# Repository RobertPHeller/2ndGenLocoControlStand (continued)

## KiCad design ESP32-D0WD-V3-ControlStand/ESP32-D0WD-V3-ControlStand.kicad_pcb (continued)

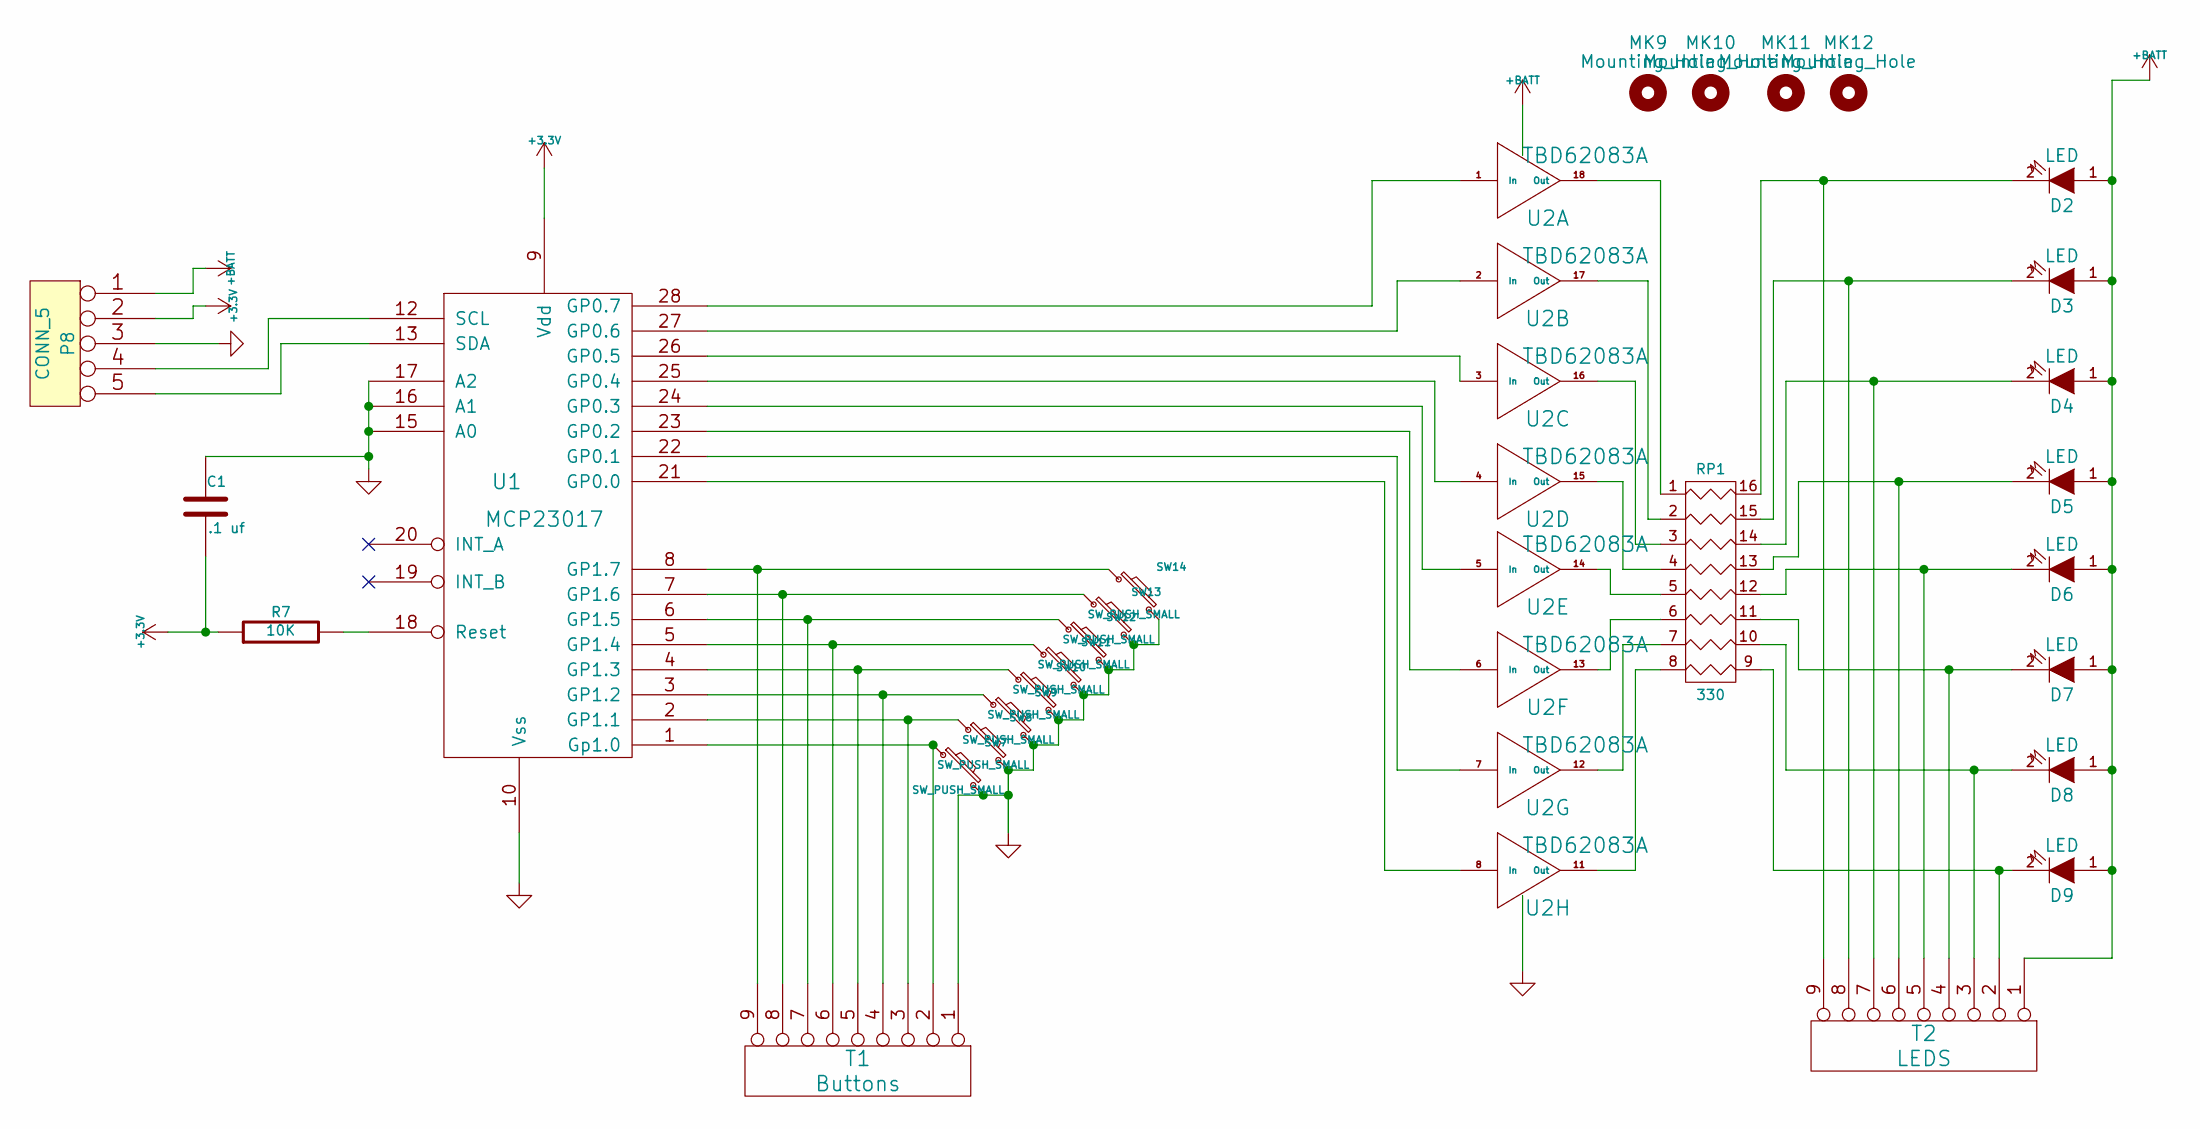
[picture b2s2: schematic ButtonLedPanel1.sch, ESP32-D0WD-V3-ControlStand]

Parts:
C1: .1 uf; C_0603; Mouser Part Number 710-885012206095
D2, D3, D4, D5, D6, D7, D8, D9: LED; LED_D5.0mm
MK9, MK10, MK11, MK12: Mounting_Hole; MountingHole_2.5mm
P8: CONN_5; Pin_Header_Angled_1x05_Pitch2.54mm; Mouser Part Number 649-1012937990501BLF
R7: 10K; R_0402; Mouser Part Number 603-RC0402JR-0710KL
RP1: 330; 4816P; Mouser Part Number 652-4816P-T1LF-330
SW7, SW8, SW9, SW10, SW11, SW12, SW13, SW14: SW_PUSH_SMALL; SW_PUSH_6mm; Mouser Part Number 179-TS026660BK160LCR
T1: Buttons; TerminalBlock_Pheonix_MPT-2.54mm_9pol; Mouser Part Number 651-1725724
T2: LEDS; TerminalBlock_Pheonix_MPT-2.54mm_9pol; Mouser Part Number 651-1725724
U1: MCP23017; SOIC-28W_7.5x17.9mm_Pitch1.27mm; Mouser Part Number 579-MCP23017-E/SO
U2: TBD62083A; SOIC-18W_7.5x11.6mm_Pitch1.27mm; Mouser Part Number 757-TBD62083AFG

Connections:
+3V3: C1.2, P8.2, R7.1, U1.9 (Vdd); also elsewhere on the board
+BATT: D2.1 (A), D3.1 (A), D4.1 (A), D5.1 (A), D6.1 (A), D7.1 (A), D8.1 (A), D9.1 (A), P8.1, T2.1, U2.10 (OC); also elsewhere on the board
GND: C1.1, P8.3, SW7.2, SW8.2, SW9.2, SW10.2, SW11.2, SW12.2, SW13.2, SW14.2, T1.1, U1.10 (Vss), U1.15 (A0), U1.16 (A1), U1.17 (A2), U2.9 (IC); also elsewhere on the board
unnamed: D2.2 (K), RP1.16 (R1), T2.9
unnamed: D3.2 (K), RP1.15 (R2), T2.8
unnamed: D4.2 (K), RP1.14 (R3), T2.7
unnamed: D5.2 (K), RP1.13 (R4), T2.6
unnamed: D6.2 (K), RP1.12 (R5), T2.5
unnamed: D7.2 (K), RP1.11 (R6), T2.4
unnamed: D8.2 (K), RP1.10 (R7), T2.3
unnamed: D9.2 (K), RP1.9 (R8), T2.2
unnamed: P8.4, U1.12 (SCL)
unnamed: P8.5, U1.13 (SDA)
unnamed: R7.2, U1.18 (Reset)
unnamed: RP1.1, U2.18 (Out)
unnamed: RP1.2, U2.17 (Out)
unnamed: RP1.3, U2.16 (Out)
unnamed: RP1.4, U2.15 (Out)
unnamed: RP1.5, U2.14 (Out)
unnamed: RP1.6, U2.13 (Out)
unnamed: RP1.7, U2.12 (Out)
unnamed: RP1.8, U2.11 (Out)
unnamed: SW7.1, T1.2, U1.1 (Gp1.0)
unnamed: SW8.1, T1.3, U1.2 (GP1.1)
unnamed: SW9.1, T1.4, U1.3 (GP1.2)
unnamed: SW10.1, T1.5, U1.4 (GP1.3)
unnamed: SW11.1, T1.6, U1.5 (GP1.4)
unnamed: SW12.1, T1.7, U1.6 (GP1.5)
unnamed: SW13.1, T1.8, U1.7 (GP1.6)
unnamed: SW14.1, T1.9, U1.8 (GP1.7)
unnamed: U1.21 (GP0.0), U2.8 (In)
unnamed: U1.22 (GP0.1), U2.7 (In)
unnamed: U1.23 (GP0.2), U2.6 (In)
unnamed: U1.24 (GP0.3), U2.5 (In)
unnamed: U1.25 (GP0.4), U2.4 (In)
unnamed: U1.26 (GP0.5), U2.3 (In)
unnamed: U1.27 (GP0.6), U2.2 (In)
unnamed: U1.28 (GP0.7), U2.1 (In)

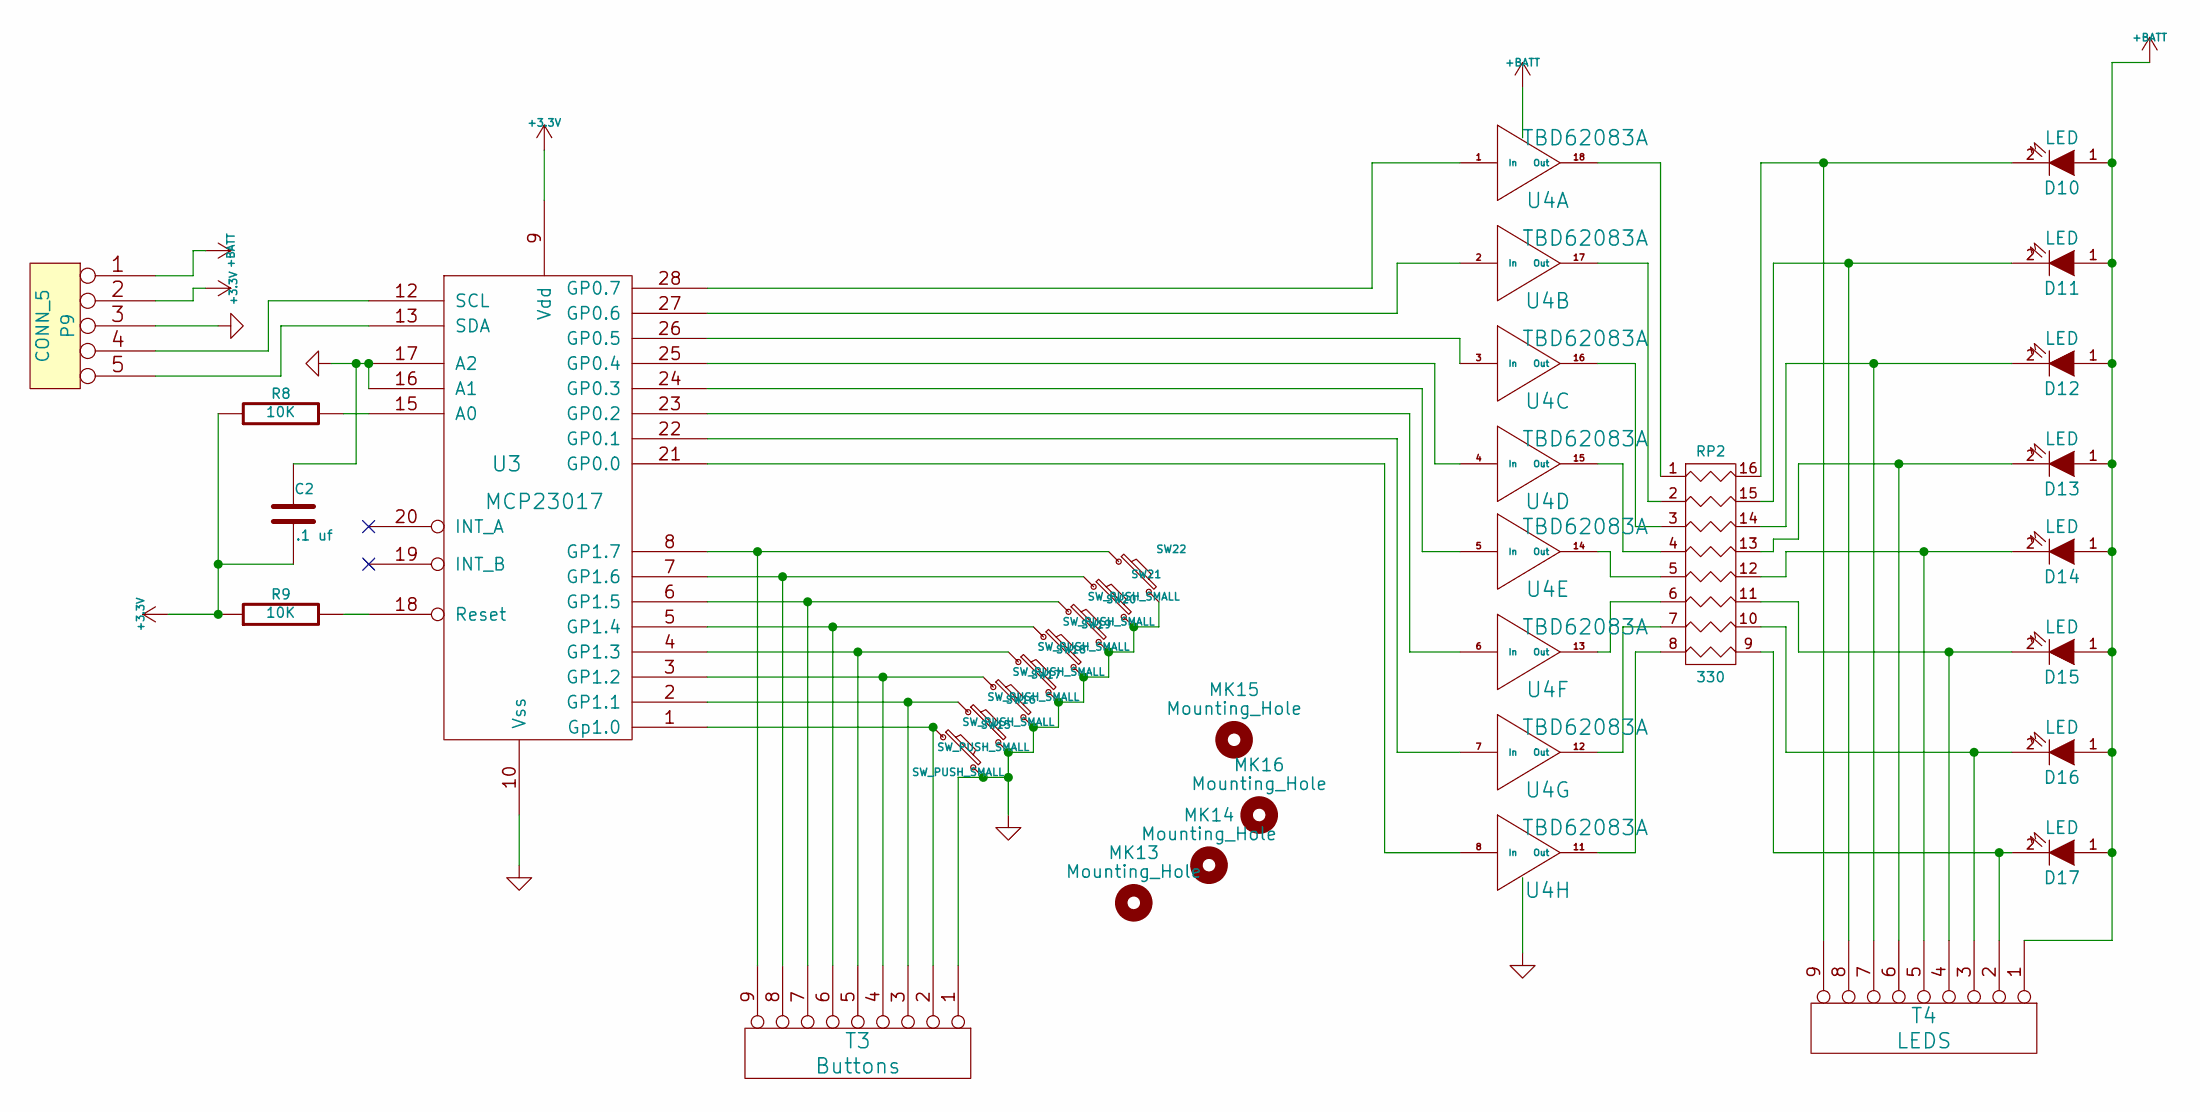
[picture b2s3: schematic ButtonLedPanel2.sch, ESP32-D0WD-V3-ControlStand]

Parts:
C2: .1 uf; C_0603; Mouser Part Number 710-885012206095
D10, D11, D12, D13, D14, D15, D16, D17: LED; LED_D5.0mm
MK13, MK14, MK15, MK16: Mounting_Hole; MountingHole_2.5mm
P9: CONN_5; Pin_Header_Angled_1x05_Pitch2.54mm; Mouser Part Number 649-1012937990501BLF
R8, R9: 10K; R_0402; Mouser Part Number 603-RC0402JR-0710KL
RP2: 330; 4816P; Mouser Part Number 652-4816P-T1LF-330
SW15, SW16, SW17, SW18, SW19, SW20, SW21, SW22: SW_PUSH_SMALL; SW_PUSH_6mm; Mouser Part Number 179-TS026660BK160LCR
T3: Buttons; TerminalBlock_Pheonix_MPT-2.54mm_9pol; Mouser Part Number 651-1725724
T4: LEDS; TerminalBlock_Pheonix_MPT-2.54mm_9pol; Mouser Part Number 651-1725724
U3: MCP23017; SOIC-28W_7.5x17.9mm_Pitch1.27mm; Mouser Part Number 79-MCP23017-E/SO
U4: TBD62083A; SOIC-18W_7.5x11.6mm_Pitch1.27mm; Mouser Part Number 757-TBD62083AFG

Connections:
+3V3: C2.2, P9.2, R8.1, R9.1, U3.9 (Vdd); also elsewhere on the board
+BATT: D10.1 (A), D11.1 (A), D12.1 (A), D13.1 (A), D14.1 (A), D15.1 (A), D16.1 (A), D17.1 (A), P9.1, T4.1, U4.10 (OC); also elsewhere on the board
GND: C2.1, P9.3, SW15.2, SW16.2, SW17.2, SW18.2, SW19.2, SW20.2, SW21.2, SW22.2, T3.1, U3.10 (Vss), U3.16 (A1), U3.17 (A2), U4.9 (IC); also elsewhere on the board
unnamed: D10.2 (K), RP2.16 (R1), T4.9
unnamed: D11.2 (K), RP2.15 (R2), T4.8
unnamed: D12.2 (K), RP2.14 (R3), T4.7
unnamed: D13.2 (K), RP2.13 (R4), T4.6
unnamed: D14.2 (K), RP2.12 (R5), T4.5
unnamed: D15.2 (K), RP2.11 (R6), T4.4
unnamed: D16.2 (K), RP2.10 (R7), T4.3
unnamed: D17.2 (K), RP2.9 (R8), T4.2
unnamed: P9.4, U3.12 (SCL)
unnamed: P9.5, U3.13 (SDA)
unnamed: R8.2, U3.15 (A0)
unnamed: R9.2, U3.18 (Reset)
unnamed: RP2.1, U4.18 (Out)
unnamed: RP2.2, U4.17 (Out)
unnamed: RP2.3, U4.16 (Out)
unnamed: RP2.4, U4.15 (Out)
unnamed: RP2.5, U4.14 (Out)
unnamed: RP2.6, U4.13 (Out)
unnamed: RP2.7, U4.12 (Out)
unnamed: RP2.8, U4.11 (Out)
unnamed: SW15.1, T3.2, U3.1 (Gp1.0)
unnamed: SW16.1, T3.3, U3.2 (GP1.1)
unnamed: SW17.1, T3.4, U3.3 (GP1.2)
unnamed: SW18.1, T3.5, U3.4 (GP1.3)
unnamed: SW19.1, T3.6, U3.5 (GP1.4)
unnamed: SW20.1, T3.7, U3.6 (GP1.5)
unnamed: SW21.1, T3.8, U3.7 (GP1.6)
unnamed: SW22.1, T3.9, U3.8 (GP1.7)
unnamed: U3.21 (GP0.0), U4.8 (In)
unnamed: U3.22 (GP0.1), U4.7 (In)
unnamed: U3.23 (GP0.2), U4.6 (In)
unnamed: U3.24 (GP0.3), U4.5 (In)
unnamed: U3.25 (GP0.4), U4.4 (In)
unnamed: U3.26 (GP0.5), U4.3 (In)
unnamed: U3.27 (GP0.6), U4.2 (In)
unnamed: U3.28 (GP0.7), U4.1 (In)

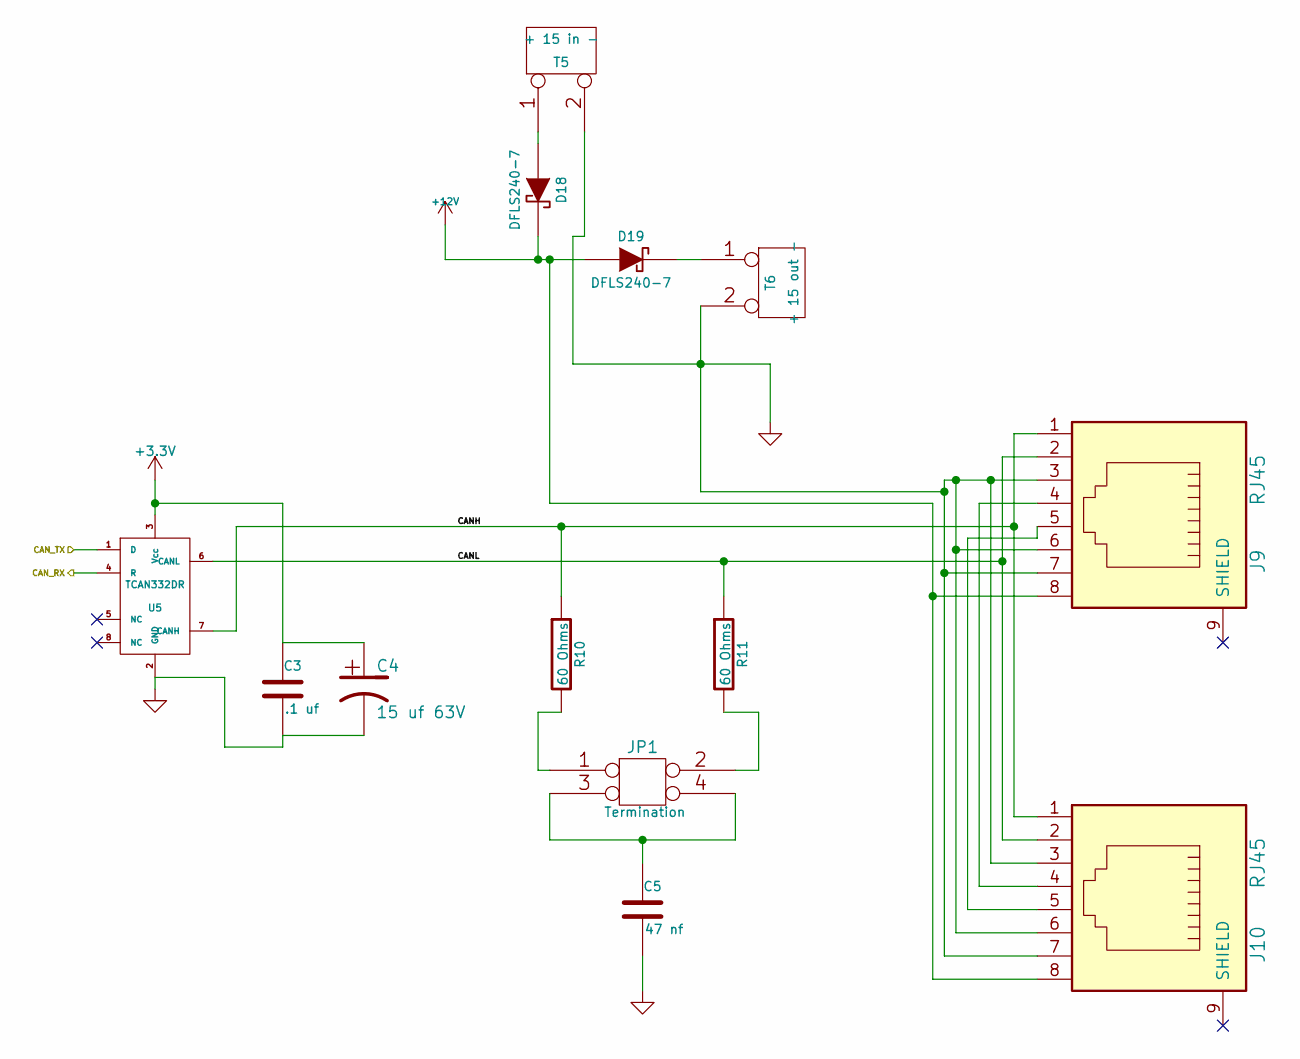
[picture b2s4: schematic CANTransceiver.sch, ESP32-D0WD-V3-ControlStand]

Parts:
C3: .1 uf; C_0603; Mouser Part Number 710-885012206095
C4: 15 uf 63V; CP_Elec_4x5.7; Mouser Part Number 647-UUD1C150MCL
C5: 47 nf; C_0603; Mouser Part Number 710-885012206093
D18, D19: DFLS240-7; D_PowerDI-123; Mouser Part Number 621-DFLS240-7
J9, J10: RJ45; RJ45_8N-S; Mouser Part Number 710-615008144221
JP1: Termination; Pin_Header_Straight_2x02_Pitch2.54mm; Mouser Part Number 649-67997-404HLF
R10, R11: 60 Ohms; R_1206; Mouser Part Number 71-CRCW120660R0KNAIF
T5: + 15 in -; TerminalBlock_Pheonix_MPT-2.54mm_2pol; Mouser Part Number 651-1725656
T6: + 15 out -; TerminalBlock_Pheonix_MPT-2.54mm_2pol; Mouser Part Number 651-1725656
U5: TCAN332DR; SOIC-8_3.9x4.9mm_Pitch1.27mm; Mouser Part Number 595-TCAN332DR

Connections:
+3V3: C3.1, C4.1, U5.3 (Vcc); also elsewhere on the board
+12V: D18.2 (K), D19.1 (A), J9.8, J10.8; also elsewhere on the board
/CAN Transceiver/CANH: J9.1, J10.1, R10.1, U5.7 (CANH)
/CAN Transceiver/CANL: J9.2, J10.2, R11.1, U5.6 (CANL)
/CAN_RX: U5.4 (R); also elsewhere on the board
/CAN_TX: U5.1 (D); also elsewhere on the board
GND: C3.2, C4.2, C5.2, J9.3, J9.6, J9.7, J10.3, J10.6, J10.7, T5.2 (PM), T6.2 (PM), U5.2 (GND); also elsewhere on the board
unnamed: C5.1, JP1.3, JP1.4
unnamed: D18.1 (A), T5.1
unnamed: D19.2 (K), T6.1
unnamed: J9.4, J10.4
unnamed: J9.5, J10.5
unnamed: JP1.1, R10.2
unnamed: JP1.2, R11.2

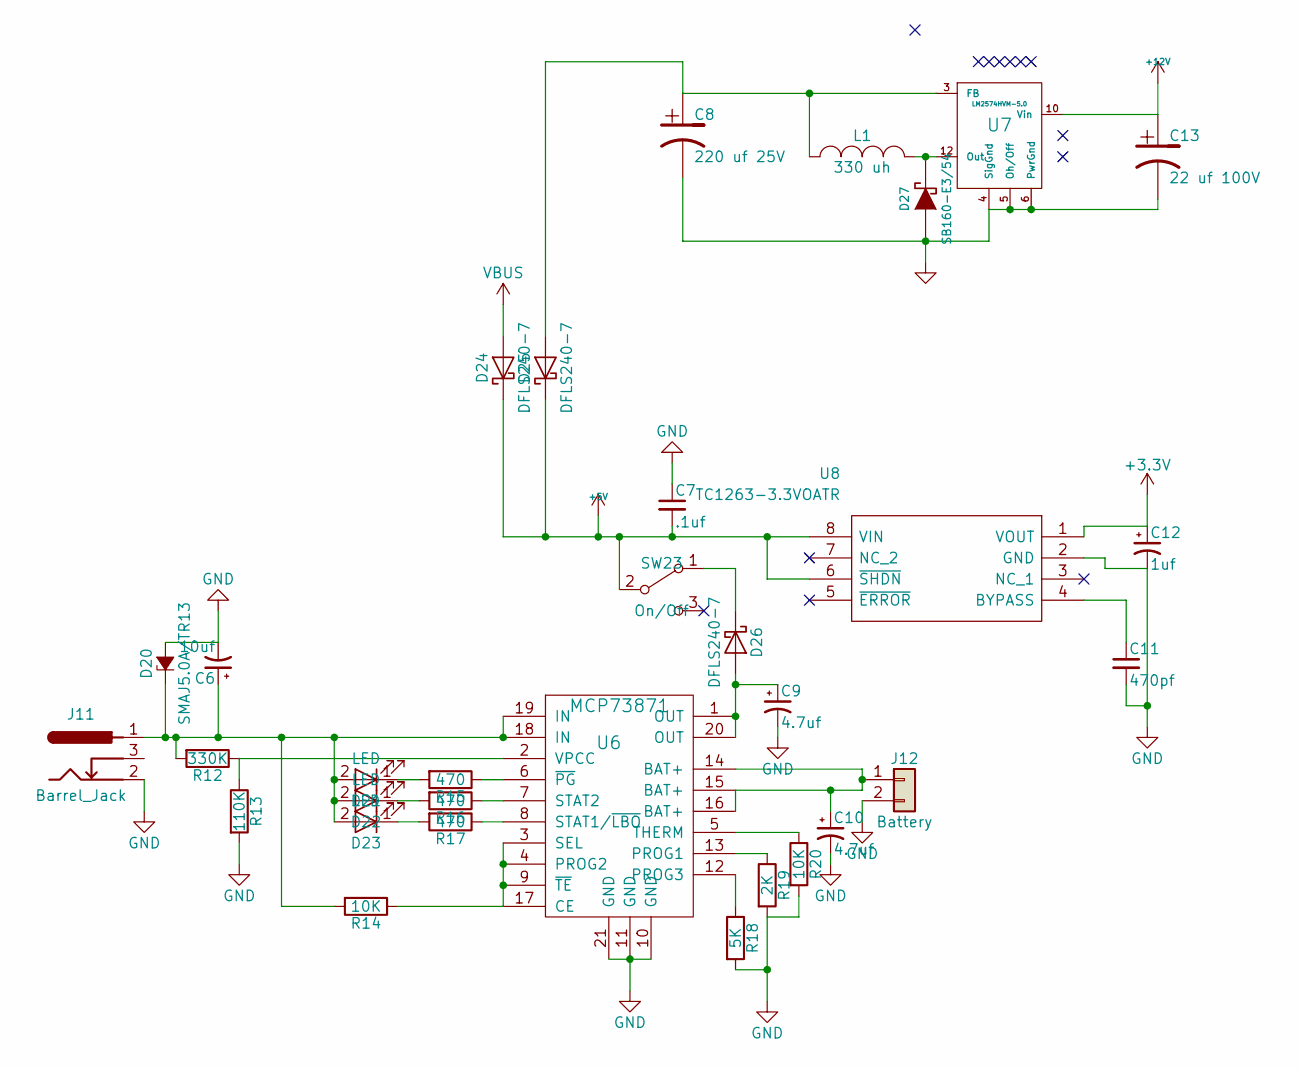
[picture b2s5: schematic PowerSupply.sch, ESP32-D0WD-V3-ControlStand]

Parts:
C6: 10uf; CP_Elec_4x5.7; Mouser Part Number 710-865080340001
C7: .1uf; C_0402; Mouser Part Number 81-GRM155R62A104KE4J
C8: 220 uf 25V; CP_Elec_8x10; Mouser Part Number 647-UWT1E221MNL1GS
C9, C10: 4.7uf; CP_Elec_4x5.7; Mouser Part Number 710-865080640004
C11: 470pf; C_0402; Mouser Part Number 80-C0402C471K4RAUTO
C12: 1uf; C_0603_POL; Mouser Part Number 74-TMCJ1C105MTRF
C13: 22 uf 100V; CP_Elec_8x10; Mouser Part Number 647-UUX2A220MNL6GS
D20: SMAJ5.0A/TR13; D_SMA; Mouser Part Number 603-SMAJ5.0A/TR13
D21: LED; LED_0402; Mouser Part Number 710-150040GS73220
D22: LED; LED_0402; Mouser Part Number 710-150040YS73220
D23: LED; LED_0402; Mouser Part Number 710-150040RS73220
D24, D25, D26: DFLS240-7; D_PowerDI-123; Mouser Part Number 621-DFLS240-7
D27: SB160-E3/54; D_SMB; Mouser Part Number 610-CMSH1-60TR13
J11: Barrel_Jack; BARREL_JACK; Mouser Part Number 992-CON-SOCJ-2155
J12: Battery; JST_PH_B2B-PH-SM4-TB_02x2.00mm_Straight; Manufacturer_Part_Number B2B-PH-SM4-TB
L1: 330 uh; SRN1060; Mouser Part Number 652-SRN1060-331M
R12: 330K; R_0402; Mouser Part Number 603-AF0402FR-07330KL
R13: 110K; R_0402; Mouser Part Number 603-RC0402JR-13110KL
R14, R20: 10K; R_0402; Mouser Part Number 603-RC0402JR-0710KL
R15, R16, R17: 470; R_0402; Mouser Part Number 603-RC0402JR-07470RL
R18: 5K; R_0402; Mouser Part Number 603-RC0402FR-075KL
R19: 2K; R_0402; Mouser Part Number 603-RC0402FR-132KL
SW23: On/Off; SW_SPDT_CK-JS102011SAQN; Mouser Part Number 611-JS102011SAQN
U6: MCP73871; QFN-20-1EP_4x4mm_Pitch0.5mm; Mouser Part Number 579-MCP73871-3CAI/ML
U7: LM2574HVM-5.0; SOIC-14_7.4x8.7mm_Pitch1.27mm; Mouser Part Number 926-LM2574HVM5.0NOPB
U8: TC1263-3.3VOATR; SO-8_5.3x6.2mm_Pitch1.27mm; Manufacturer_Part_Number TC1263-3.3VOATR

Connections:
+3V3: C12.1, U8.1 (VOUT); also elsewhere on the board
+5V: C7.2, D24.1 (K), D25.1 (K), SW23.2 (B), U8.6 (~SHDN), U8.8 (VIN); also elsewhere on the board
+12V: C13.1, U7.10 (Vin); also elsewhere on the board
GND: C6.2, C7.1, C8.2, C9.2, C10.2, C11.2, C12.2, C13.2, D20.2 (A), D27.1 (A), J11.2, J12.2, R13.2, R18.2, R19.2, R20.2, U6.10 (GND), U6.11 (GND), U6.21 (GND), U7.4 (SigGnd), U7.5 (Oh/Off), U7.6 (PwrGnd), U8.2 (GND); also elsewhere on the board
unnamed: C6.1, D20.1 (K), D21.2 (A), D22.2 (A), D23.2 (A), J11.1, R12.2, R14.2, U6.18 (IN), U6.19 (IN)
unnamed: C8.1, D25.2 (A), L1.1, U7.3 (FB)
unnamed: C9.1, D26.2 (A), U6.1 (OUT), U6.20 (OUT)
unnamed: C10.1, J12.1, U6.14 (BAT+), U6.15 (BAT+), U6.16 (BAT+)
unnamed: C11.1, U8.4 (BYPASS)
unnamed: D21.1 (K), R15.2
unnamed: D22.1 (K), R16.2
unnamed: D23.1 (K), R17.2
unnamed: D26.1 (K), SW23.1 (A)
unnamed: D27.2 (K), L1.2, U7.12 (Out)
unnamed: R12.1, R13.1, U6.2 (VPCC)
unnamed: R14.1, U6.3 (SEL), U6.4 (PROG2), U6.9 (~TE), U6.17 (CE)
unnamed: R15.1, U6.6 (~PG)
unnamed: R16.1, U6.7 (STAT2)
unnamed: R17.1, U6.8 (STAT1/~LBO)
unnamed: R18.1, U6.12 (PROG3)
unnamed: R19.1, U6.13 (PROG1)
unnamed: R20.1, U6.5 (THERM)
VBUS: D24.2 (A); also elsewhere on the board

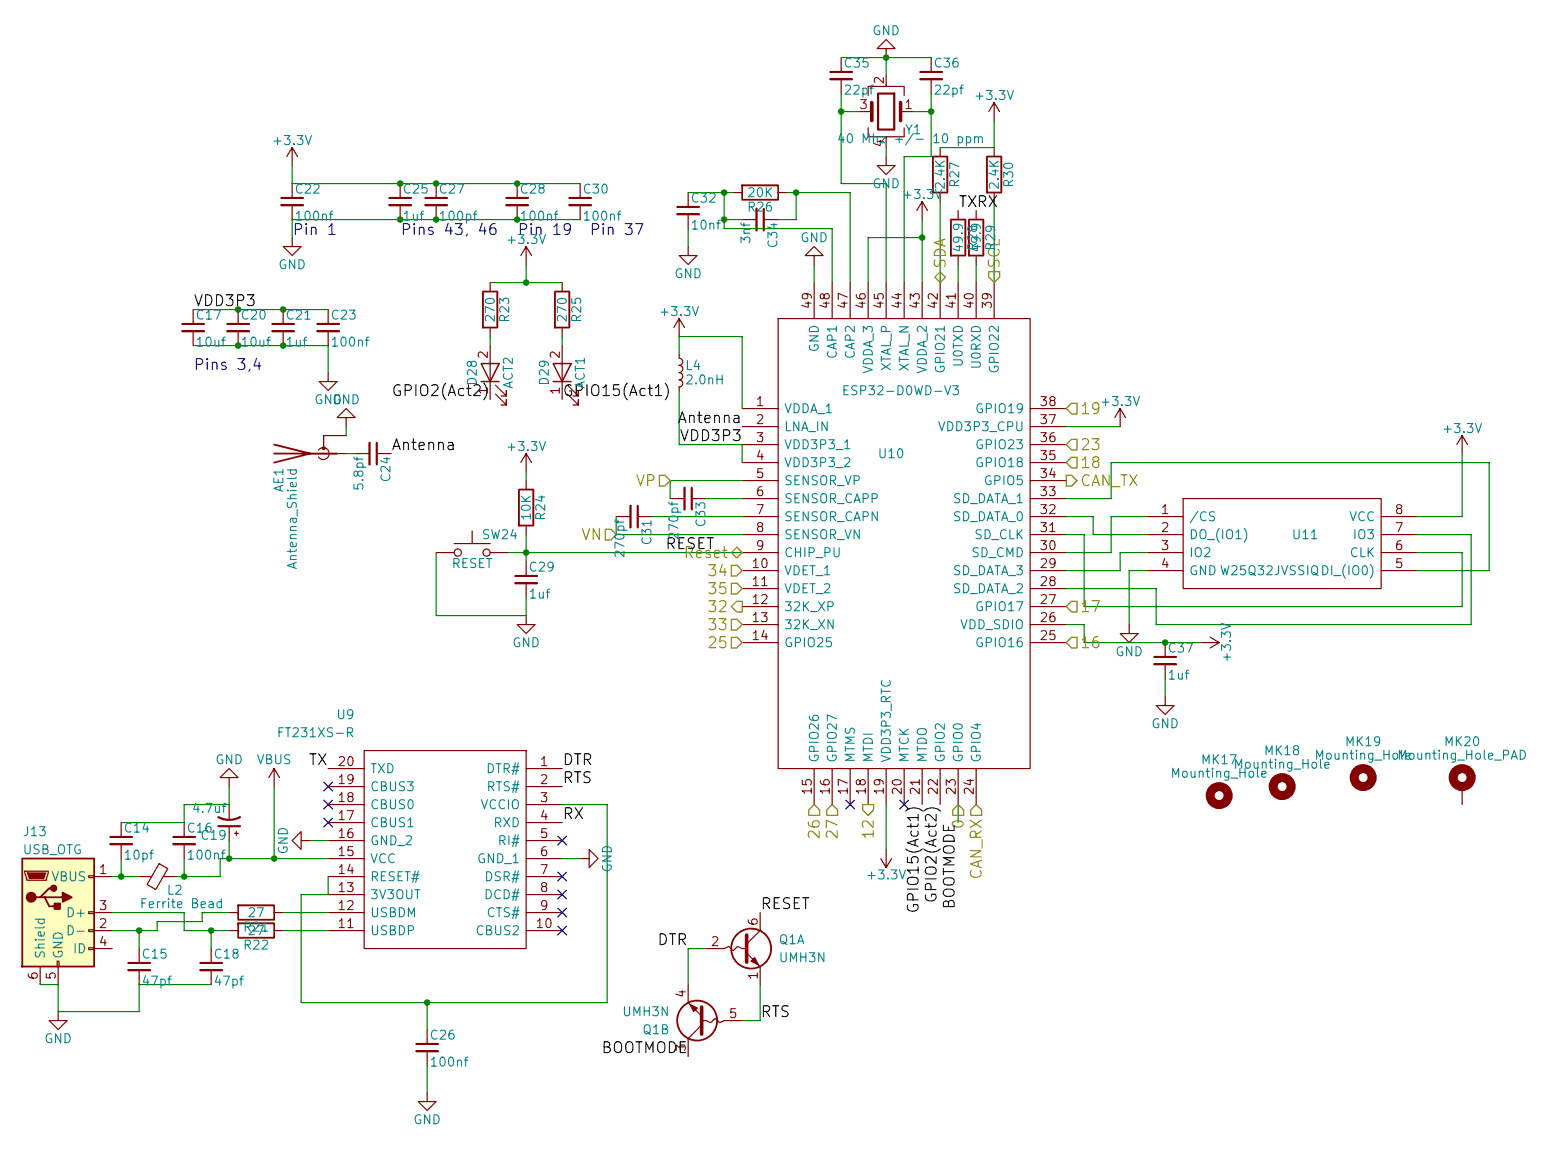
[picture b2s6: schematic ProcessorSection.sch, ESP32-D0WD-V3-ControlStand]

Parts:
AE1: Antenna_Shield; Antenna
C14: 10pf; C_0402; Mouser Part Number 80-C0402C100K5RAUTO
C15, C18: 47pf; C_0402; Mouser Part Number 80-C0402C470K5RAUTO
C16, C26: 100nf; C_0402; Mouser Part Number 80-C0402C104K8R
C17, C20: 10uf; C_0805; Mouser Part Number 187-CL21A106MQFNNNE
C19: 4.7uf; CP_Elec_4x5.7; Mouser Part Number 710-865080540002
C21, C25, C29, C37: 1uf; C_0402; Mouser Part Number 80-C0402C101K8RAUTO
C22, C23, C28, C30: 100nf; C_0402; Mouser Part Number 710-885012105001
C24: 5.8pf; C_0402
C27: 100pf; C_0402; Mouser Part Number 80-C0402C101K3RAUTO
C31, C33: 270pf; C_0402
C32: 10nf; C_0402; Mouser Part Number 81-GRM155R61E103KA1D
C34: 3nf; C_0402; Mouser Part Number 81-GRM1557U1A302JA1D
C35, C36: 22pf; C_0402; Mouser Part Number 187-CL05C220JB5NNND
D28: ACT2; LED_0402; Mouser Part Number 710-150040SS73220
D29: ACT1; LED_0402; Mouser Part Number 710-150040GS73220
J13: USB_OTG; USB_Micro-B_Molex_47346-0001; Mouser Part Number 538-47346-0001
L2: Ferrite Bead; L_0402; Mouser Part Number 810-MMZ1005S800CTD25
L4: 2.0nH; L_0402; Mouser Part Number 810-MLG1005S2N0ST000
MK17, MK18, MK19: Mounting_Hole; MountingHole_2.5mm
MK20: Mounting_Hole_PAD; MountingHole_2.5mm_Pad
Q1: UMH3N; SOT-363_SC-70-6; Mouser Part Number 755-UMH3NFHATN
R21, R22: 27; R_0402; Mouser Part Number 603-RT0402FRE0727RL
R23, R25: 270; R_0402; Mouser Part Number 754-RR0510P-271D
R24: 10K; R_0402; Mouser Part Number 603-RC0402JR-1310KL
R26: 20K; R_0402; Mouser Part Number 791-RMC10K203FTH
R27, R30: 2.4K; R_0402; Mouser Part Number 71-CRCW06032K40JNEAC
R28, R29: 49.9; R_0402; Mouser Part Number 791-RMC1/16SK49R9FTH
SW24: RESET; PTS647SM38SMTR2LFS; Mouser Part Number 611-PTS647SN70SMTR2L
U9: FT231XS-R; SSOP-20_5.3x7.2mm_Pitch0.65mm; Manufacturer_Part_Number FT231XS-R
U10: ESP32-D0WD-V3; QFN35P500X500X90-49N-D; Manufacturer_Part_Number ESP32-D0WD-V3; Mouser Part Number 356-ESP32-D0WD-V3
U11: W25Q32JVSSIQ; SOIC-8_3.9x4.9mm_Pitch1.27mm; Mouser Part Number 454-W25Q32JVSSIQ
Y1: 40 Mhz +/- 10 ppm; FA20_H; Mouser Part Number 732-FA-20H40MF10Z-W3

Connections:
+3V3: C22.1, C25.1, C27.1, C28.1, C30.1, C37.1, L4.1, R23.1, R24.1, R25.1, R27.1, R30.1, U10.1 (VDDA_1), U10.19 (VDD3P3_RTC), U10.26 (VDD_SDIO), U10.37 (VDD3P3_CPU), U10.43 (VDDA_2), U10.46 (VDDA_3), U11.8 (VCC); also elsewhere on the board
/Bell: U10.15 (GPIO26); also elsewhere on the board
/Brake: C31.2, U10.8 (SENSOR_VN); also elsewhere on the board
/Button_A: U10.10 (VDET_1); also elsewhere on the board
/Button_B: U10.11 (VDET_2); also elsewhere on the board
/Button_C: U10.13 (32K_XN); also elsewhere on the board
/Button_D: U10.14 (GPIO25); also elsewhere on the board
/CAN_RX: U10.24 (GPIO4); also elsewhere on the board
/CAN_TX: U10.34 (GPIO5); also elsewhere on the board
/Horn: C33.2, U10.5 (SENSOR_VP); also elsewhere on the board
/L_Bright: U10.25 (GPIO16); also elsewhere on the board
/L_Dim: U10.27 (GPIO17); also elsewhere on the board
/L_Ditch: Q1.3 (C2), U10.23 (GPIO0); also elsewhere on the board
/L_Off: U10.35 (GPIO18); also elsewhere on the board
/Processor Section/Antenna: C24.1, U10.2 (LNA_IN)
/Processor Section/DTR: Q1.2 (B1), Q1.4 (E2), U9.1 (DTR#)
/Processor Section/GPIO2(Act2): D28.1 (K), U10.22 (GPIO2)
/Processor Section/GPIO15(Act1): D29.1 (K), U10.21 (MTDO)
/Processor Section/RTS: Q1.1 (E1), Q1.5 (B2), U9.2 (RTS#)
/Processor Section/RX: R29.1, U9.4 (RXD)
/Processor Section/TX: R28.1, U9.20 (TXD)
/Processor Section/VDD3P3: C17.1, C20.1, C21.1, C23.1, L4.2, U10.3 (VDD3P3_1), U10.4 (VDD3P3_2)
/RST: C29.1, Q1.6 (C1), R24.2, SW24.2, U10.9 (CHIP_PU)
/Reverser: U10.16 (GPIO27); also elsewhere on the board
/SCL: R30.2, U10.39 (GPIO22); also elsewhere on the board
/SDA: R27.2, U10.42 (GPIO21); also elsewhere on the board
/Status_G: U10.12 (32K_XP); also elsewhere on the board
/Status_R: U10.18 (MTDI); also elsewhere on the board
/ThrottleA: U10.36 (GPIO23); also elsewhere on the board
/ThrottleB: U10.38 (GPIO19); also elsewhere on the board
GND: AE1.2 (Shield), C14.1, C15.2, C16.1, C17.2, C18.2, C19.2, C20.2, C21.2, C22.2, C23.2, C25.2, C26.2, C27.2, C28.2, C29.2, C30.2, C32.2, C35.1, C36.1, C37.2, J13.5 (GND), J13.6 (Shield), SW24.1, U9.6 (GND_1), U9.16 (GND_2), U10.49 (GND), U11.4 (GND), Y1.2, Y1.4; also elsewhere on the board
unnamed: AE1.1 (A), C24.2
unnamed: C14.2, J13.1 (VBUS), L2.2
unnamed: C15.1, J13.2 (D-), R21.2
unnamed: C18.1, J13.3 (D+), R22.2
unnamed: C26.1, U9.3 (VCCIO), U9.13 (3V3OUT), U9.14 (RESET#)
unnamed: C31.1, U10.7 (SENSOR_CAPN)
unnamed: C32.1, C34.2, R26.2, U10.48 (CAP1)
unnamed: C33.1, U10.6 (SENSOR_CAPP)
unnamed: C34.1, R26.1, U10.47 (CAP2)
unnamed: C35.2, U10.45 (XTAL_P), Y1.3
unnamed: C36.2, U10.44 (XTAL_N), Y1.1
unnamed: D28.2 (A), R23.2
unnamed: D29.2 (A), R25.2
unnamed: R21.1, U9.12 (USBDM)
unnamed: R22.1, U9.11 (USBDP)
unnamed: R28.2, U10.41 (U0TXD)
unnamed: R29.2, U10.40 (U0RXD)
unnamed: U10.28 (SD_DATA_2), U11.7 (IO3)
unnamed: U10.29 (SD_DATA_3), U11.3 (IO2)
unnamed: U10.30 (SD_CMD), U11.1 (/CS)
unnamed: U10.31 (SD_CLK), U11.6 (CLK)
unnamed: U10.32 (SD_DATA_0), U11.2 (DO_(IO1))
unnamed: U10.33 (SD_DATA_1), U11.5 (DI_(IO0))
VBUS: C16.2, C19.1, L2.1, U9.15 (VCC); also elsewhere on the board

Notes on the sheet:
Pins 3,4
Pin 1
Pins 43, 46
Pin 19
Pin 37

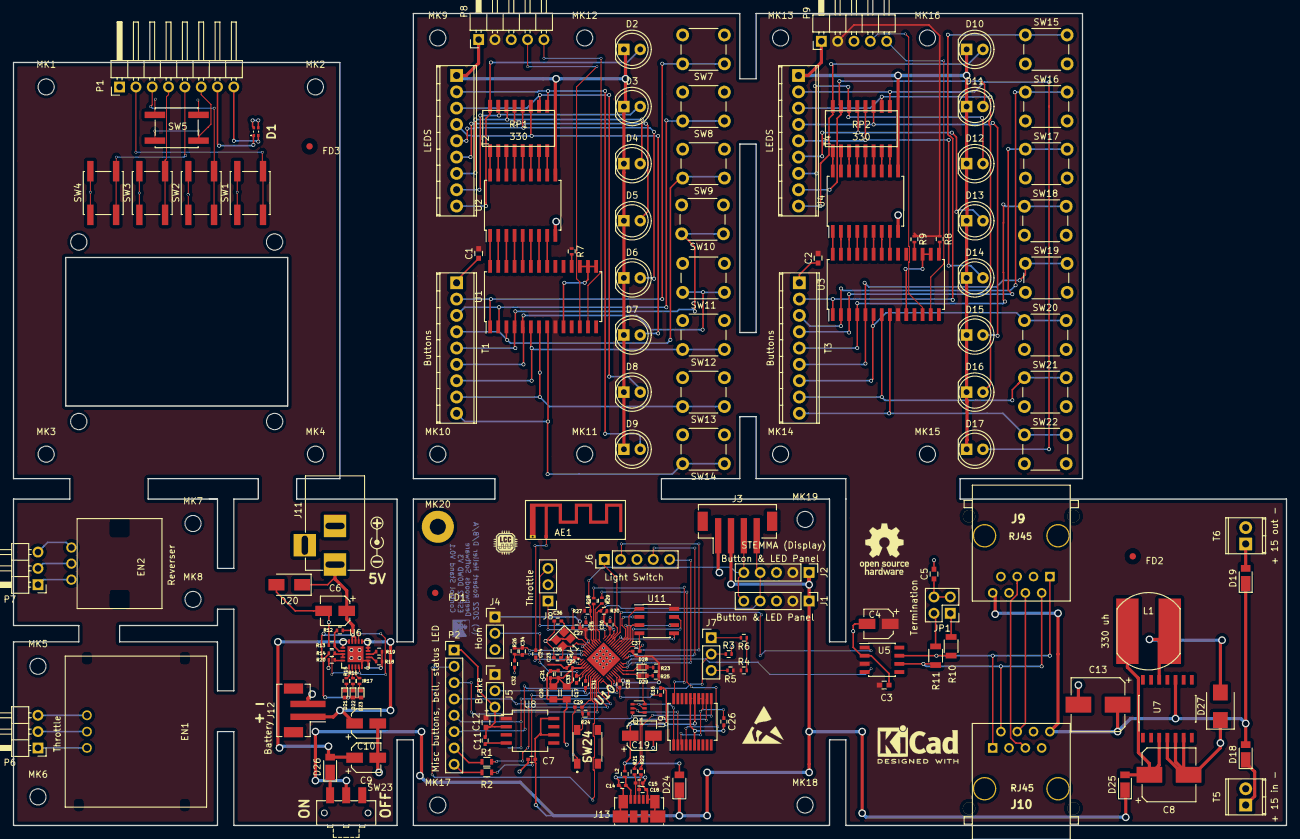
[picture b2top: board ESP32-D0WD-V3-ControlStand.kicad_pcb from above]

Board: 2 copper layers, 198.1 x 126.4 mm, 189 parts (0 on the bottom side), 174 nets.

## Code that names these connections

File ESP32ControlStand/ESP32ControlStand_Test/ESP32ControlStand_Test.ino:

// -!- C++ -!- //////////////////////////////////////////////////////////////
//
//  System        : 
//  Module        : 
//  Object Name   : $RCSfile$
//  Revision      : $Revision$
//  Date          : $Date$
//  Author        : $Author$
//  Created By    : Robert Heller
//  Created       : Sun Oct 6 09:53:58 2019
//  Last Modified : <191012.1543>
//
//  Description	
//
//  Notes
//
//  History
//	
/////////////////////////////////////////////////////////////////////////////
//
//    Copyright (C) 2019  Robert Heller D/B/A Deepwoods Software
//			51 Locke Hill Road
//			Wendell, MA 01379-9728
//
//    This program is free software; you can redistribute it and/or modify
//    it under the terms of the GNU General Public License as published by
//    the Free Software Foundation; either version 2 of the License, or
//    (at your option) any later version.
//
//    This program is distributed in the hope that it will be useful,
//    but WITHOUT ANY WARRANTY; without even the implied warranty of
//    MERCHANTABILITY or FITNESS FOR A PARTICULAR PURPOSE.  See the
//    GNU General Public License for more details.
//
//    You should have received a copy of the GNU General Public License
//    along with this program; if not, write to the Free Software
//    Foundation, Inc., 675 Mass Ave, Cambridge, MA 02139, USA.
//
// 
//
//////////////////////////////////////////////////////////////////////////////

#include <Arduino.h>
#include <SPI.h>
#include <Wire.h>
#include <Adafruit_GFX.h>
#include <Adafruit_SSD1306.h>
#include <Adafruit_MCP23017.h>

#define HORN      A0
#define BRAKE     A3
#define BUTTON_A  34
#define BUTTON_B  35
#define BUTTON_C  33
#define BUTTON_D  25
#define BELL      26
#define REVERSER  A17
#define STATUS_R  12
#define STATUS_G  32
#define THROTTLEA 22
#define THROTTLEB 19
#define L_OFF     18
#define L_DIM     17
#define L_BRIGHT  16
#define L_DITCH    0

#define SCREEN_WIDTH 128 // OLED display width, in pixels
#define SCREEN_HEIGHT 32 // OLED display height, in pixels

// Declaration for an SSD1306 display connected to I2C (SDA, SCL pins)
#define OLED_RESET     -1 // Reset pin # (or -1 if sharing Arduino reset pin)
Adafruit_SSD1306 display(SCREEN_WIDTH, SCREEN_HEIGHT, &Wire, OLED_RESET);

Adafruit_MCP23017 mcp;

uint8_t throttlePosition = 0;
uint8_t throttleQuadrature;

void checkThrottle()
{
    uint8_t newQuadrature;
    newQuadrature = digitalRead(THROTTLEA) | (digitalRead(THROTTLEB) << 1);
    uint8_t quadratureUp[] = {1, 3, 0, 2};
    uint8_t quadratureDown[] = {2, 0, 3, 1};
    if (newQuadrature != throttleQuadrature)
    {
        if (newQuadrature == quadratureUp[throttleQuadrature & 0x03])
        {
            if (throttlePosition > 0)
                throttlePosition--;
        }
        else if (newQuadrature == quadratureDown[throttleQuadrature & 0x03])
        {
            if (throttlePosition < 8)
                throttlePosition++;
        }
        else
            throttlePosition = 0;
    }
    throttleQuadrature = newQuadrature & 0x03;
}

uint16_t readBrake() {
    return analogRead(BRAKE);
}

uint16_t readHorn() {
    return analogRead(HORN);
}

uint16_t readReverser() {
    return analogRead(REVERSER);
}

uint8_t StatusColor = 1;

uint8_t LedNumber = -1;

uint16_t LedUpdateCount = 100;

static const char rcsid[] = "@(#) : $Id$";

void setup() {
    // put your setup code here, to run once:
    Serial.begin(9600);
    
    // SSD1306_SWITCHCAPVCC = generate display voltage from 3.3V internally
    if(!display.begin(SSD1306_SWITCHCAPVCC, 0x3C)) { // Address 0x3C for 128x32
        Serial.println(F("SSD1306 allocation failed"));
        for(;;); // Don't proceed, loop forever
    }
    pinMode(HORN,INPUT);
    pinMode(BRAKE,INPUT);
    pinMode(BUTTON_A,INPUT_PULLUP);
    pinMode(BUTTON_B,INPUT_PULLUP);
    pinMode(BUTTON_C,INPUT_PULLUP);
    pinMode(BUTTON_D,INPUT_PULLUP);
    pinMode(BELL,INPUT_PULLUP);
    pinMode(REVERSER,INPUT);
    pinMode(STATUS_R,OUTPUT);
    digitalWrite(STATUS_R,LOW);
    pinMode(STATUS_G,OUTPUT);
    digitalWrite(STATUS_G,LOW);
    pinMode(THROTTLEA,INPUT_PULLUP);
    pinMode(THROTTLEB,INPUT_PULLUP);
    throttleQuadrature = digitalRead(THROTTLEA) | (digitalRead(THROTTLEB) << 1);
    pinMode(L_OFF,INPUT_PULLUP);
    pinMode(L_DIM,INPUT_PULLUP);
    pinMode(L_BRIGHT,INPUT_PULLUP);
    pinMode(L_DITCH,INPUT_PULLUP);
    mcp.begin();
    for (int i=0; i< 8; i++) {
        mcp.pinMode(i,OUTPUT);  // LED i
        mcp.digitalWrite(i,LOW);
        mcp.pinMode(i+8,INPUT_PULLUP); // Button i
    }
    // Show initial display buffer contents on the screen --
    // the library initializes this with an Adafruit splash screen.
    display.display();
    delay(2000); // Pause for 2 seconds
    
    // Clear the buffer
    display.clearDisplay();
    display.setTextSize(1);
    display.setTextColor(WHITE);
    display.cp437(true);
}
                
void loop() {
    // put your main code here, to run repeatedly:
    if (LedUpdateCount >= 100) {
        if (LedNumber >= 0) {
            mcp.digitalWrite(LedNumber,LOW);
        }
        LedNumber++;
        if (LedNumber >= 8) LedNumber = 0;
        mcp.digitalWrite(LedNumber,HIGH);
        switch (StatusColor) {
        case 0:
            digitalWrite(STATUS_R,LOW);
            digitalWrite(STATUS_G,LOW);
            break;
        case 1:
            digitalWrite(STATUS_R,HIGH);
            digitalWrite(STATUS_G,LOW);
            break;
        case 2:
            digitalWrite(STATUS_R,LOW);
            digitalWrite(STATUS_G,HIGH);
            break;
        case 3:
            digitalWrite(STATUS_R,HIGH);
            digitalWrite(STATUS_G,HIGH);
            break;
        }
        StatusColor++;
        if (StatusColor > 3) StatusColor = 0;
        LedUpdateCount = 0;
    }
    display.clearDisplay();
    display.setCursor(0, 0);
    checkThrottle();
    display.print("Throttle: ");display.println(throttlePosition);
    display.print("Brake:    ");display.println(readBrake());
    display.print("Horn:     ");display.println(readHorn());
    display.print("Reverser: ");display.println(readReverser());
    display.display();
    LedUpdateCount++;
    delay(10);
}    

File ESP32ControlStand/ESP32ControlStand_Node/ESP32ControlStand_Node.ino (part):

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/// the onboard flash.
/// Note: If you are using a pin other than 4 you will likely need to adjust
/// the GPIO pin definitions for the outputs.
constexpr gpio_num_t CAN_RX_PIN = GPIO_NUM_4;

/// This is the ESP32 pin connected to the SN65HVD23x/MCP2551 D (TX) pin.
/// Recommended pins: 5, 17, 22.
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/// the onboard flash and 34-39 which are input only.
/// Note: If you are using a pin other than 5 you will likely need to adjust
/// the GPIO pin definitions for the outputs.
constexpr gpio_num_t CAN_TX_PIN = GPIO_NUM_5;

#endif // USE_CAN

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void setup() {
    Serial.begin(115200L);
    // Set up status LED Early and show Yellow (starting up)
    pinMode(STATUS_R,OUTPUT);
    digitalWrite(STATUS_R,HIGH);
    pinMode(STATUS_G,OUTPUT);
    digitalWrite(STATUS_G,HIGH);
    
    
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#if defined(USE_CAN)
    // Add the hardware CAN device as a bridge
    openmrn.add_can_port(
        new Esp32HardwareCan("esp32can", CAN_RX_PIN, CAN_TX_PIN));
#endif // USE_CAN
    stand.welcomeScreen();
    stand.SendIsTrainEventQuery();
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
